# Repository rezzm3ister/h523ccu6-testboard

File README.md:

# h523ccu6-testboard
test board for h523ccu6 mcu

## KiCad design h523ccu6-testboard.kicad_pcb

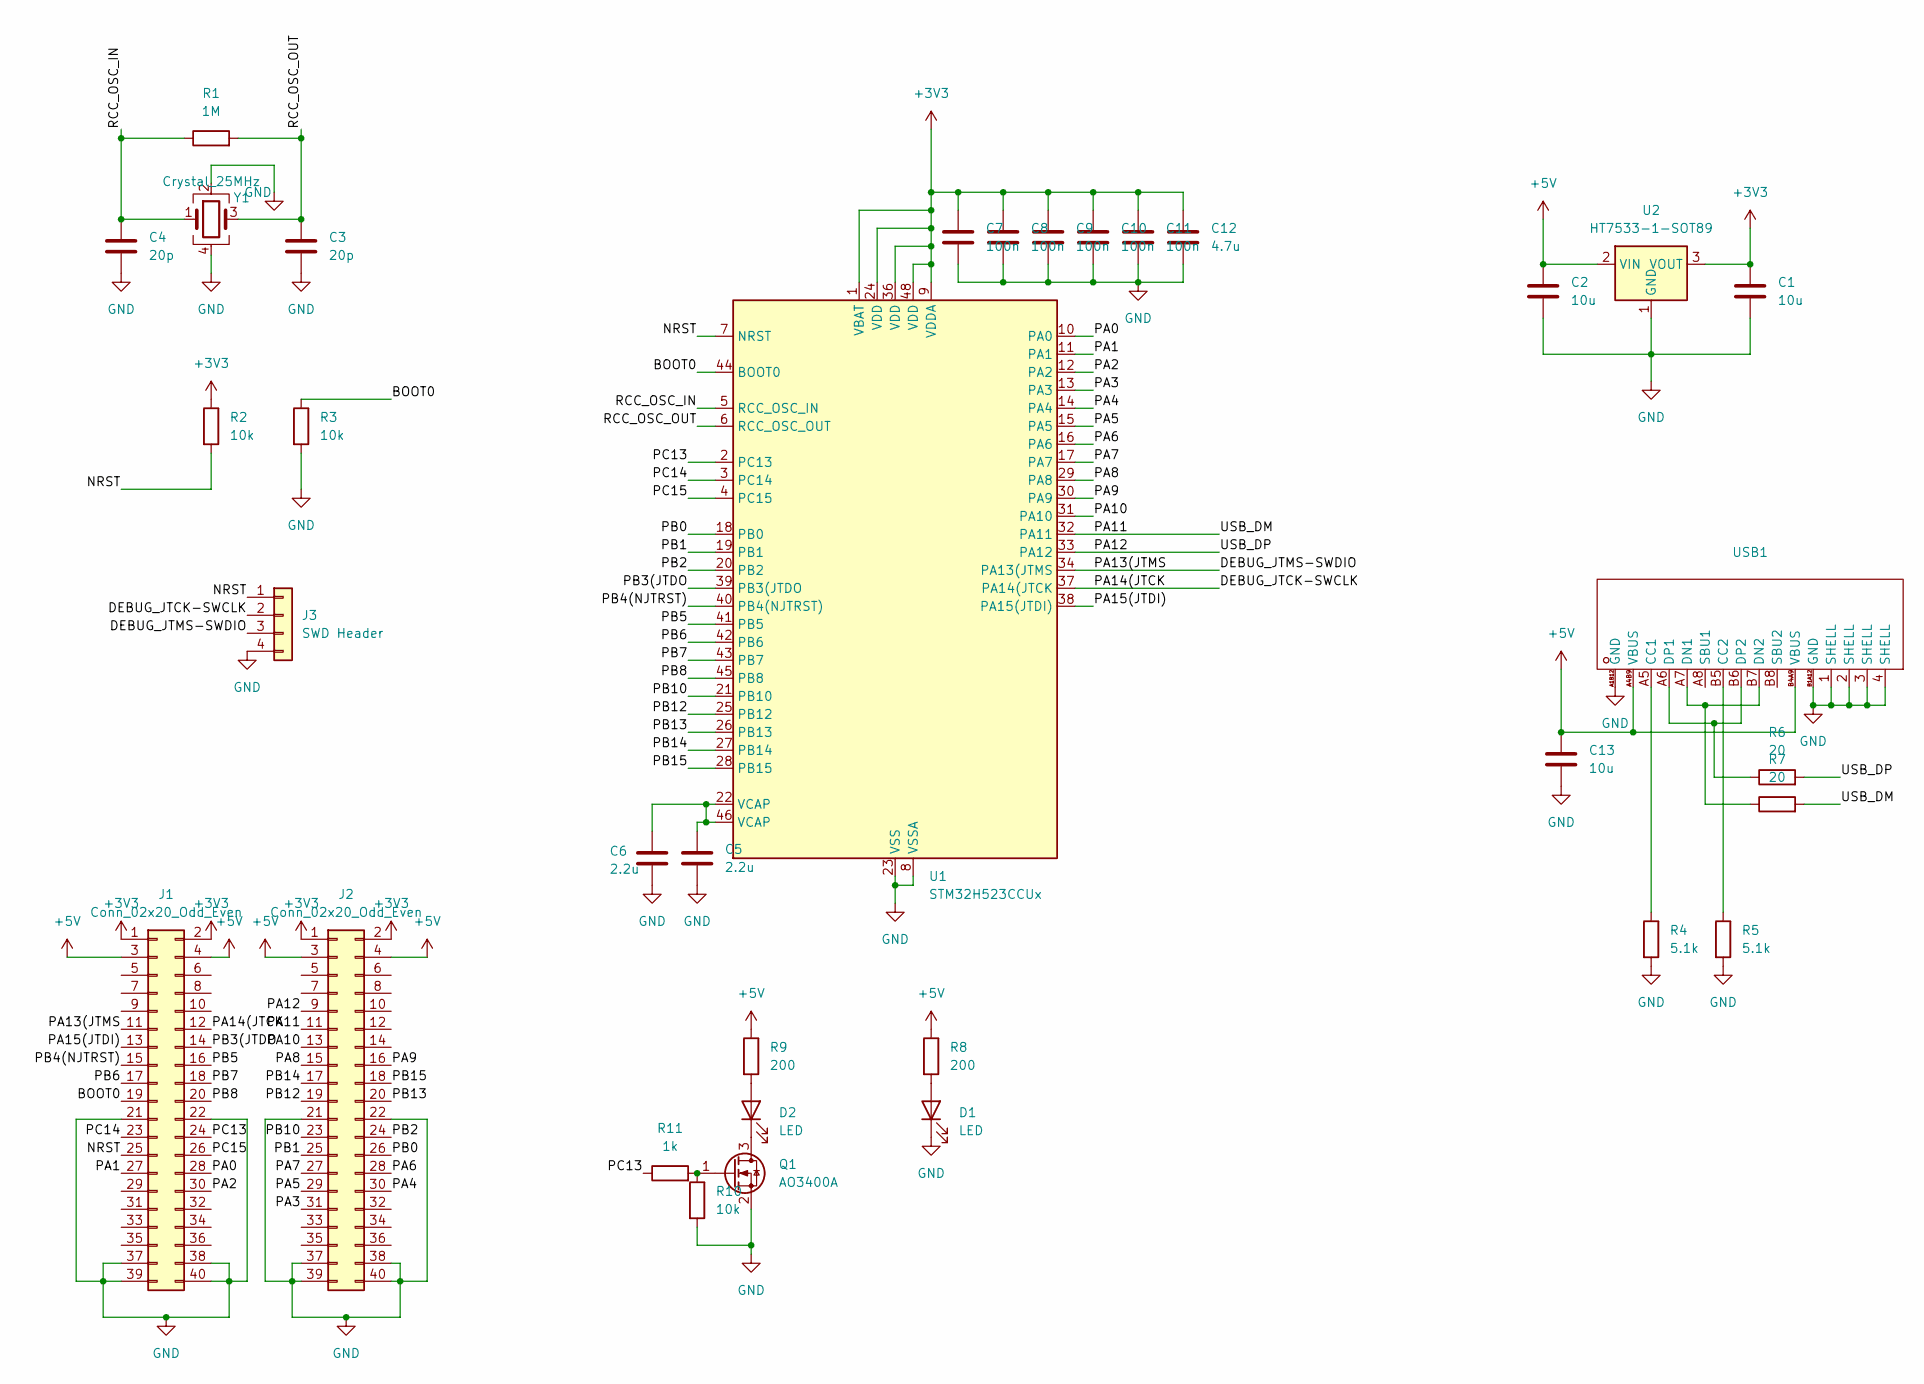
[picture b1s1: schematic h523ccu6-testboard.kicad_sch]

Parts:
C1, C2, C13: 10u; C_0603_1608Metric; LCSC C19702
C3, C4: 20p; C_0402_1005Metric; LCSC C1554
C5, C6: 2.2u; C_0603_1608Metric; LCSC C12530
C7, C8, C9, C10, C11: 100n; C_0402_1005Metric; LCSC C1525
C12: 4.7u; C_0603_1608Metric; LCSC C19666
D1, D2: LED; LED_0603_1608Metric; LCSC C2286
J1, J2: Conn_02x20_Odd_Even; PinHeader_2x20_P2.54mm_Vertical
J3: SWD Header; PinHeader_1x04_P2.54mm_Vertical
Q1: AO3400A; SOT-23; LCSC C20917
R1: 1M; R_0402_1005Metric; LCSC C26083
R2, R3, R10: 10k; R_0402_1005Metric; LCSC C25744
R4, R5: 5.1k; R_0402_1005Metric; LCSC C25905
R6, R7: 20; R_0603_1608Metric; LCSC C22950
R8, R9: 200; R_0402_1005Metric; LCSC C25087
R11: 1k; R_0402_1005Metric; LCSC C11702
U1: STM32H523CCUx; QFN-48-1EP_7x7mm_P0.5mm_EP5.6x5.6mm; LCSC C23898421
U2: HT7533-1-SOT89; SOT-89-3; LCSC C14289
USB1: USB-C-SMD_TYPE-C16PIN; Manufacturer Part TYPE-C16PIN; LCSC Part Name Type-C 母 卧贴
Y1: Crystal_25MHz; Crystal_SMD_3225-4Pin_3.2x2.5mm; LCSC C9006

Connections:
+3V3: C1.1, C7.1, C8.1, C9.1, C10.1, C11.1, C12.1, J1.1, J1.2, J2.1, J2.2, R2.1, U1.1 (VBAT), U1.9 (VDDA), U1.24 (VDD), U1.36 (VDD), U1.48 (VDD), U2.3 (VOUT)
+5V: C2.1, C13.1, J1.3, J1.4, J2.3, J2.4, R8.1, R9.1, U2.2 (VIN), USB1.A4B9 (VBUS), USB1.B4A9 (VBUS)
/BOOT0: J1.19, R3.1, U1.44 (BOOT0)
/DEBUG_JTCK-SWCLK: J1.12, J3.2, U1.37 (PA14(JTCK)
/DEBUG_JTMS-SWDIO: J1.11, J3.3, U1.34 (PA13(JTMS)
/NRST: J1.25, J3.1, R2.2, U1.7 (NRST)
/PA0: J1.28, U1.10 (PA0)
/PA1: J1.27, U1.11 (PA1)
/PA2: J1.30, U1.12 (PA2)
/PA3: J2.31, U1.13 (PA3)
/PA4: J2.30, U1.14 (PA4)
/PA5: J2.29, U1.15 (PA5)
/PA6: J2.28, U1.16 (PA6)
/PA7: J2.27, U1.17 (PA7)
/PA8: J2.15, U1.29 (PA8)
/PA9: J2.16, U1.30 (PA9)
/PA10: J2.13, U1.31 (PA10)
/PA11: J2.11, R7.2, U1.32 (PA11)
/PA12: J2.9, R6.2, U1.33 (PA12)
/PA15(JTDI): J1.13, U1.38 (PA15(JTDI))
/PB0: J2.26, U1.18 (PB0)
/PB1: J2.25, U1.19 (PB1)
/PB2: J2.24, U1.20 (PB2)
/PB3(JTDO: J1.14, U1.39 (PB3(JTDO)
/PB4(NJTRST): J1.15, U1.40 (PB4(NJTRST))
/PB5: J1.16, U1.41 (PB5)
/PB6: J1.17, U1.42 (PB6)
/PB7: J1.18, U1.43 (PB7)
/PB8: J1.20, U1.45 (PB8)
/PB10: J2.23, U1.21 (PB10)
/PB12: J2.19, U1.25 (PB12)
/PB13: J2.20, U1.26 (PB13)
/PB14: J2.17, U1.27 (PB14)
/PB15: J2.18, U1.28 (PB15)
/PC13: J1.24, R11.1, U1.2 (PC13)
/PC14: J1.23, U1.3 (PC14)
/PC15: J1.26, U1.4 (PC15)
/RCC_OSC_IN: C4.1, R1.1, U1.5 (RCC_OSC_IN), Y1.1
/RCC_OSC_OUT: C3.1, R1.2, U1.6 (RCC_OSC_OUT), Y1.3
GND: C1.2, C2.2, C3.2, C4.2, C5.2, C6.2, C7.2, C8.2, C9.2, C10.2, C11.2, C12.2, C13.2, D1.1 (K), J1.21, J1.22, J1.37, J1.38, J1.39, J1.40, J2.21, J2.22, J2.37, J2.38, J2.39, J2.40, J3.4, Q1.2 (S), R3.2, R4.2, R5.2, R10.2, U1.8 (VSSA), U1.23 (VSS), U1.35 (VSS), U1.47 (VSS), U1.49 (VSS), U2.1 (GND), USB1.1 (SHELL), USB1.2 (SHELL), USB1.3 (SHELL), USB1.4 (SHELL), USB1.A1B12 (GND), USB1.B1A12 (GND), Y1.2, Y1.4
unnamed: C5.1, C6.1, U1.22 (VCAP), U1.46 (VCAP)
unnamed: D1.2 (A), R8.2
unnamed: D2.2 (A), R9.2
unnamed: D2.1 (K), Q1.3 (D)
unnamed: Q1.1 (G), R10.1, R11.2
unnamed: R4.1, USB1.A5 (CC1)
unnamed: R5.1, USB1.B5 (CC2)
unnamed: R7.1, USB1.A7 (DN1), USB1.B7 (DN2)
unnamed: R6.1, USB1.A6 (DP1), USB1.B6 (DP2)

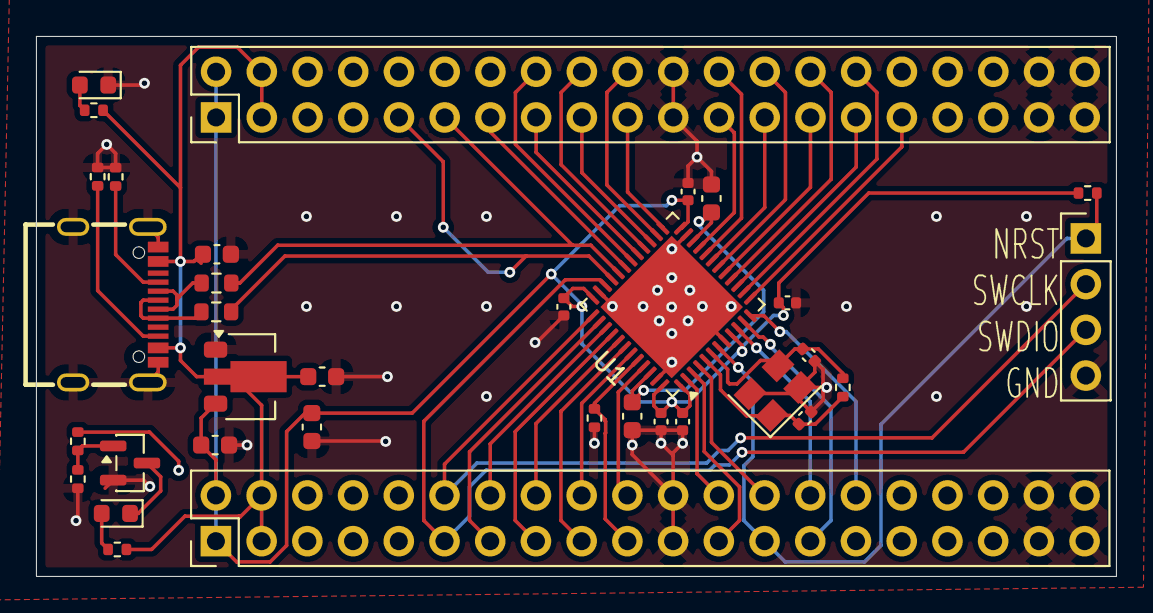
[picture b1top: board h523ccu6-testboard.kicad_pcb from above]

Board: 2 copper layers, 60.0 x 30.0 mm, 34 parts (0 on the bottom side), 49 nets.

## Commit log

2026-03-08 finished testboard
